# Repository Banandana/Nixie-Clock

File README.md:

# Nixie-Clock
A custom WIP nixie clock using IN12 tubes, HC595 shift registers, and 74141 BDC drivers

TO-DO: Add MCU to board design. Add DS1302 RTC IC for more accurate timekeeping.

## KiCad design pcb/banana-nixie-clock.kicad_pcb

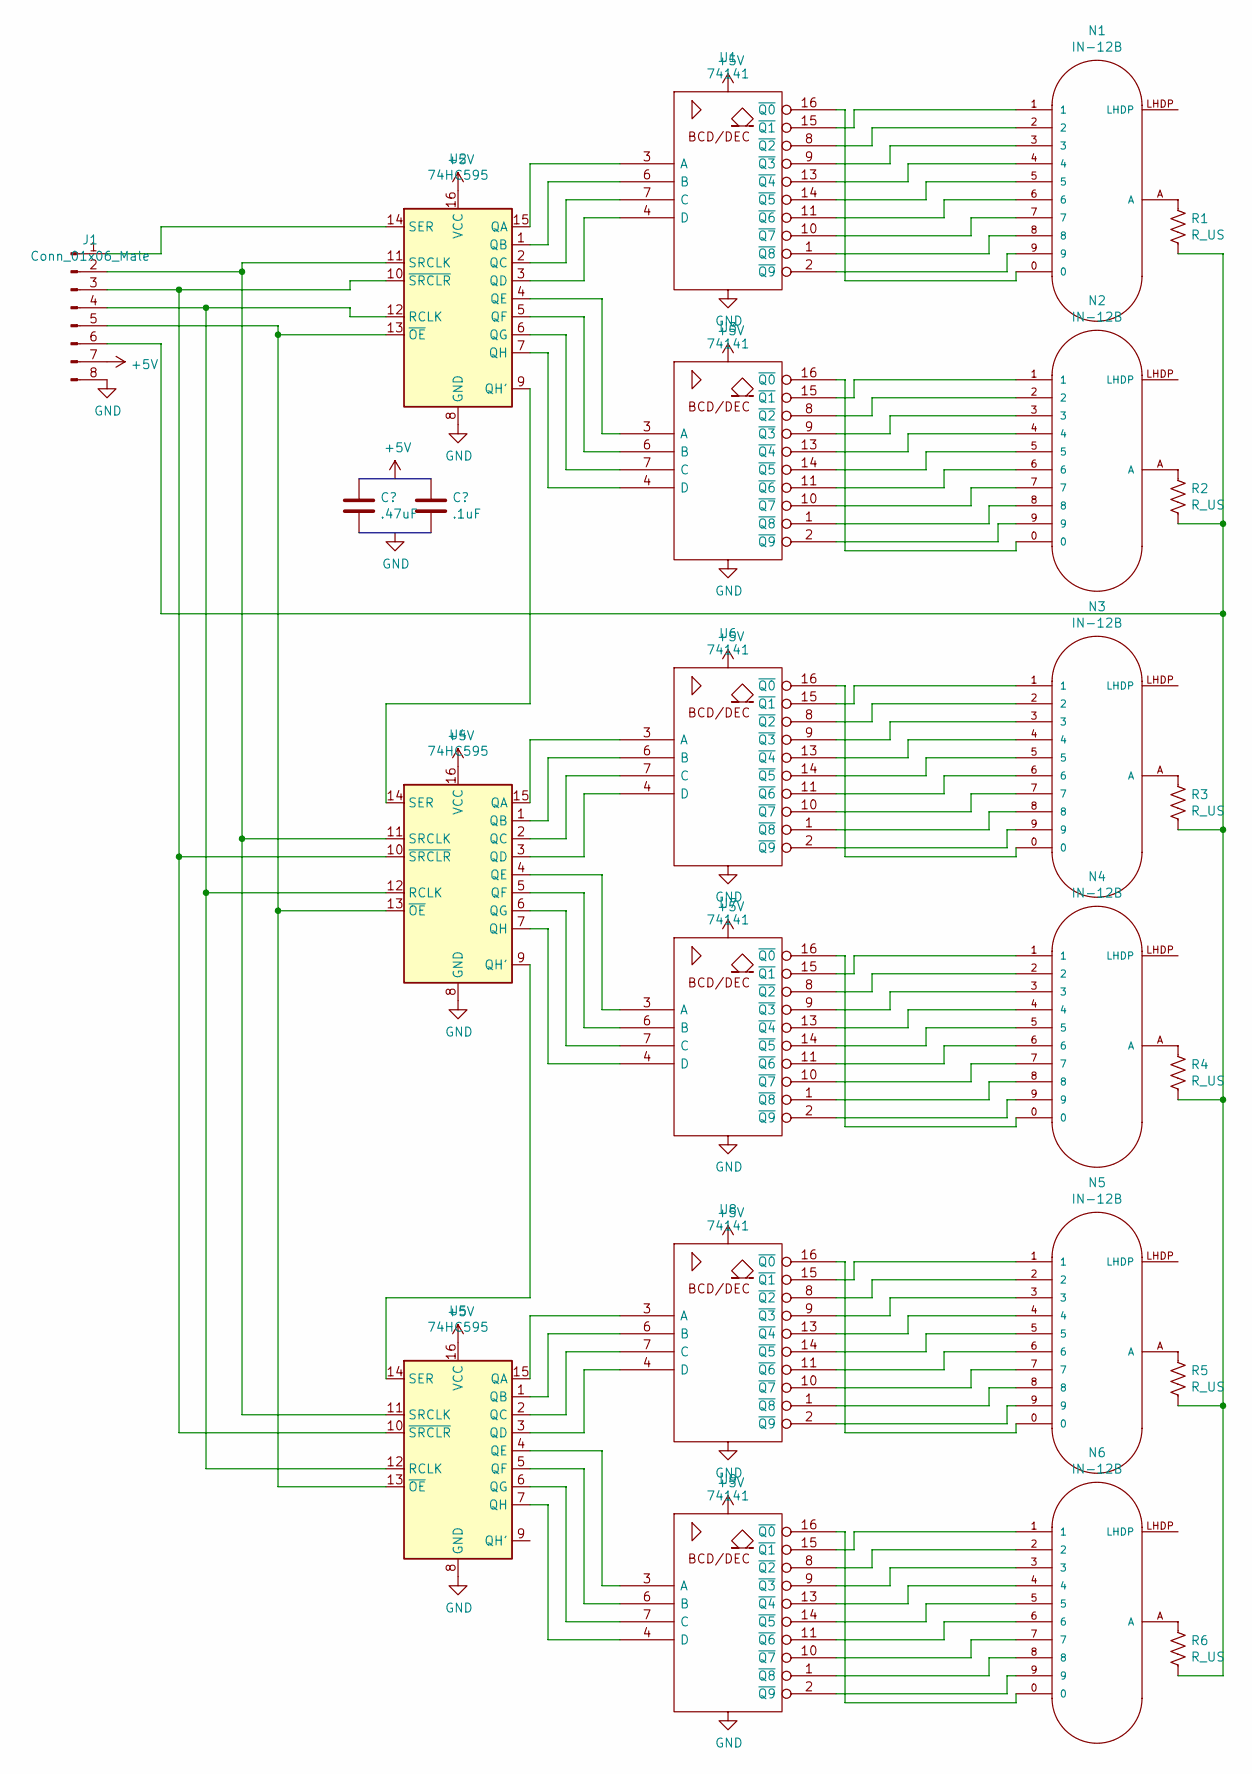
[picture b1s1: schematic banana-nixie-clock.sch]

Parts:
J1: Conn_01x06_Male; PinHeader_1x08_P2.54mm_Vertical
N1, N2, N3, N4, N5, N6: IN-12B; russian-nixies-IN-12
R1, R2, R3, R4, R5, R6: R_US; R_Box_L8.4mm_W2.5mm_P5.08mm
U1, U3, U6, U7, U8, U9: 74141; DIP-16_W7.62mm
U2, U4, U5: 74HC595; DIP-16_W7.62mm

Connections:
+5V: J1.7, U1.5 (VCC), U2.16 (VCC), U3.5 (VCC), U4.16 (VCC), U5.16 (VCC), U6.5 (VCC), U7.5 (VCC), U8.5 (VCC), U9.5 (VCC)
GND: J1.8, U1.12 (GND), U2.8 (GND), U3.12 (GND), U4.8 (GND), U5.8 (GND), U6.12 (GND), U7.12 (GND), U8.12 (GND), U9.12 (GND)
unnamed: J1.1, U2.14 (SER)
unnamed: J1.2, U2.11 (SRCLK), U4.11 (SRCLK), U5.11 (SRCLK)
unnamed: J1.3, U2.10 (~SRCLR), U4.10 (~SRCLR), U5.10 (~SRCLR)
unnamed: J1.4, U2.12 (RCLK), U4.12 (RCLK), U5.12 (RCLK)
unnamed: J1.5, U2.13 (~OE), U4.13 (~OE), U5.13 (~OE)
unnamed: J1.6, R1.2, R2.2, R3.2, R4.2, R5.2, R6.2
unnamed: N1.0, U1.16 (~Q0)
unnamed: N1.1, U1.15 (~Q1)
unnamed: N1.2, U1.8 (~Q2)
unnamed: N1.3, U1.9 (~Q3)
unnamed: N1.4, U1.13 (~Q4)
unnamed: N1.5, U1.14 (~Q5)
unnamed: N1.6, U1.11 (~Q6)
unnamed: N1.7, U1.10 (~Q7)
unnamed: N1.8, U1.1 (~Q8)
unnamed: N1.9, U1.2 (~Q9)
unnamed: N1.A, R1.1
unnamed: N2.0, U3.16 (~Q0)
unnamed: N2.1, U3.15 (~Q1)
unnamed: N2.2, U3.8 (~Q2)
unnamed: N2.3, U3.9 (~Q3)
unnamed: N2.4, U3.13 (~Q4)
unnamed: N2.5, U3.14 (~Q5)
unnamed: N2.6, U3.11 (~Q6)
unnamed: N2.7, U3.10 (~Q7)
unnamed: N2.8, U3.1 (~Q8)
unnamed: N2.9, U3.2 (~Q9)
unnamed: N2.A, R2.1
unnamed: N3.0, U6.16 (~Q0)
unnamed: N3.1, U6.15 (~Q1)
unnamed: N3.2, U6.8 (~Q2)
unnamed: N3.3, U6.9 (~Q3)
unnamed: N3.4, U6.13 (~Q4)
unnamed: N3.5, U6.14 (~Q5)
unnamed: N3.6, U6.11 (~Q6)
unnamed: N3.7, U6.10 (~Q7)
unnamed: N3.8, U6.1 (~Q8)
unnamed: N3.9, U6.2 (~Q9)
unnamed: N3.A, R3.1
unnamed: N4.0, U7.16 (~Q0)
unnamed: N4.1, U7.15 (~Q1)
unnamed: N4.2, U7.8 (~Q2)
unnamed: N4.3, U7.9 (~Q3)
unnamed: N4.4, U7.13 (~Q4)
unnamed: N4.5, U7.14 (~Q5)
unnamed: N4.6, U7.11 (~Q6)
unnamed: N4.7, U7.10 (~Q7)
unnamed: N4.8, U7.1 (~Q8)
unnamed: N4.9, U7.2 (~Q9)
unnamed: N4.A, R4.1
unnamed: N5.0, U8.16 (~Q0)
unnamed: N5.1, U8.15 (~Q1)
unnamed: N5.2, U8.8 (~Q2)
unnamed: N5.3, U8.9 (~Q3)
unnamed: N5.4, U8.13 (~Q4)
unnamed: N5.5, U8.14 (~Q5)
unnamed: N5.6, U8.11 (~Q6)
unnamed: N5.7, U8.10 (~Q7)
unnamed: N5.8, U8.1 (~Q8)
unnamed: N5.9, U8.2 (~Q9)
unnamed: N5.A, R5.1
unnamed: N6.0, U9.16 (~Q0)
unnamed: N6.1, U9.15 (~Q1)
unnamed: N6.2, U9.8 (~Q2)
unnamed: N6.3, U9.9 (~Q3)
unnamed: N6.4, U9.13 (~Q4)
unnamed: N6.5, U9.14 (~Q5)
unnamed: N6.6, U9.11 (~Q6)
unnamed: N6.7, U9.10 (~Q7)
unnamed: N6.8, U9.1 (~Q8)
unnamed: N6.9, U9.2 (~Q9)
unnamed: N6.A, R6.1
unnamed: U1.3 (A), U2.15 (QA)
unnamed: U1.4 (D), U2.3 (QD)
unnamed: U1.6 (B), U2.1 (QB)
unnamed: U1.7 (C), U2.2 (QC)
unnamed: U2.4 (QE), U3.3 (A)
unnamed: U2.5 (QF), U3.6 (B)
unnamed: U2.6 (QG), U3.7 (C)
unnamed: U2.7 (QH), U3.4 (D)
unnamed: U2.9 (QH'), U4.14 (SER)
unnamed: U4.1 (QB), U6.6 (B)
unnamed: U4.2 (QC), U6.7 (C)
unnamed: U4.3 (QD), U6.4 (D)
unnamed: U4.4 (QE), U7.3 (A)
unnamed: U4.5 (QF), U7.6 (B)
unnamed: U4.6 (QG), U7.7 (C)
unnamed: U4.7 (QH), U7.4 (D)
unnamed: U4.9 (QH'), U5.14 (SER)
unnamed: U4.15 (QA), U6.3 (A)
unnamed: U5.1 (QB), U8.6 (B)
unnamed: U5.2 (QC), U8.7 (C)
unnamed: U5.3 (QD), U8.4 (D)
unnamed: U5.4 (QE), U9.3 (A)
unnamed: U5.5 (QF), U9.6 (B)
unnamed: U5.6 (QG), U9.7 (C)
unnamed: U5.7 (QH), U9.4 (D)
unnamed: U5.15 (QA), U8.3 (A)

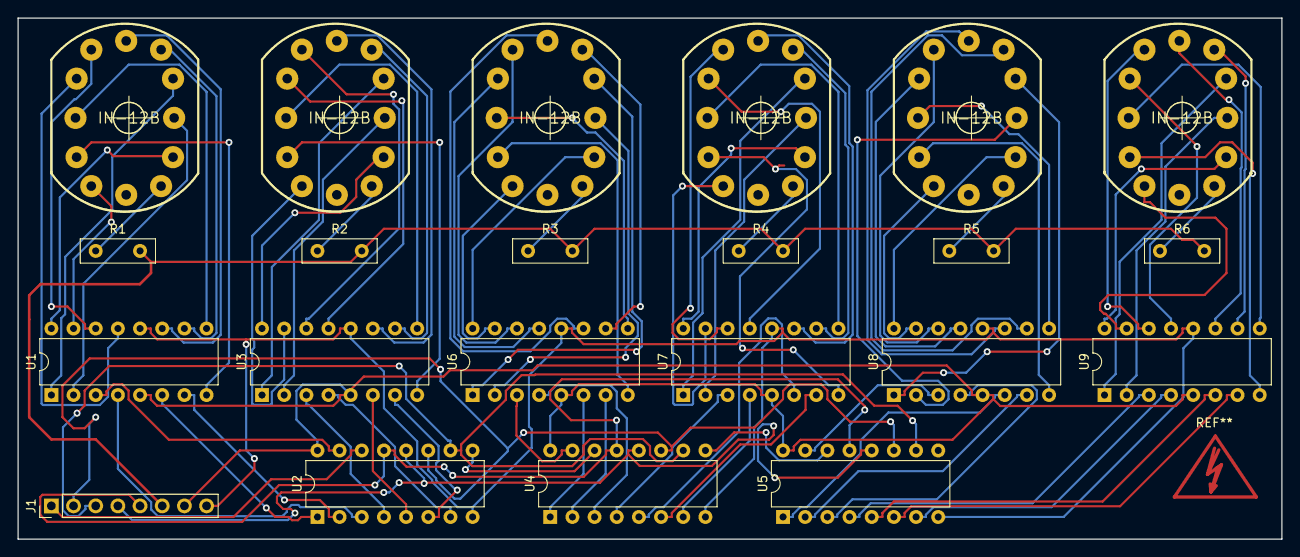
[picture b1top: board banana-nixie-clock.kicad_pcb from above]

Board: 2 copper layers, 144.8 x 59.7 mm, 22 parts (0 on the bottom side), 100 nets.

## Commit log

2019-02-03 initial commit - add pcb design and basic clock code
